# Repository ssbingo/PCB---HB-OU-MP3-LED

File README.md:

# PCB und Gehäuse für HB-OU-MP3-LED (jp112sdl)

## Bilder

## Schaltplan

[:arrow_right: Schaltplan](Images/HB-OU-MP3-LED_PCB_Schaltplan.pdf)

## Platine

[:arrow_right: PCB Gerber](Platine/HB-OU-MP3-LED_PCB.zip)

## Gehäuse

<br>

<br>

<br>

<br>

## Aufbau / Stückliste

### Der Aufbau

### Die benötigten Bauteile
| Bauteil | Link |
| --------|------|
| | |

## Hinweise

- :exclamation:

## Lizenz

**Creative Commons BY-NC-SA**<br>
Give Credit, NonCommercial, ShareAlike

<br />This work is licensed under a <a rel="license" href="http://creativecommons.org/licenses/by-nc-sa/4.0/">Creative Commons Attribution-NonCommercial-ShareAlike 4.0 International License</a>.

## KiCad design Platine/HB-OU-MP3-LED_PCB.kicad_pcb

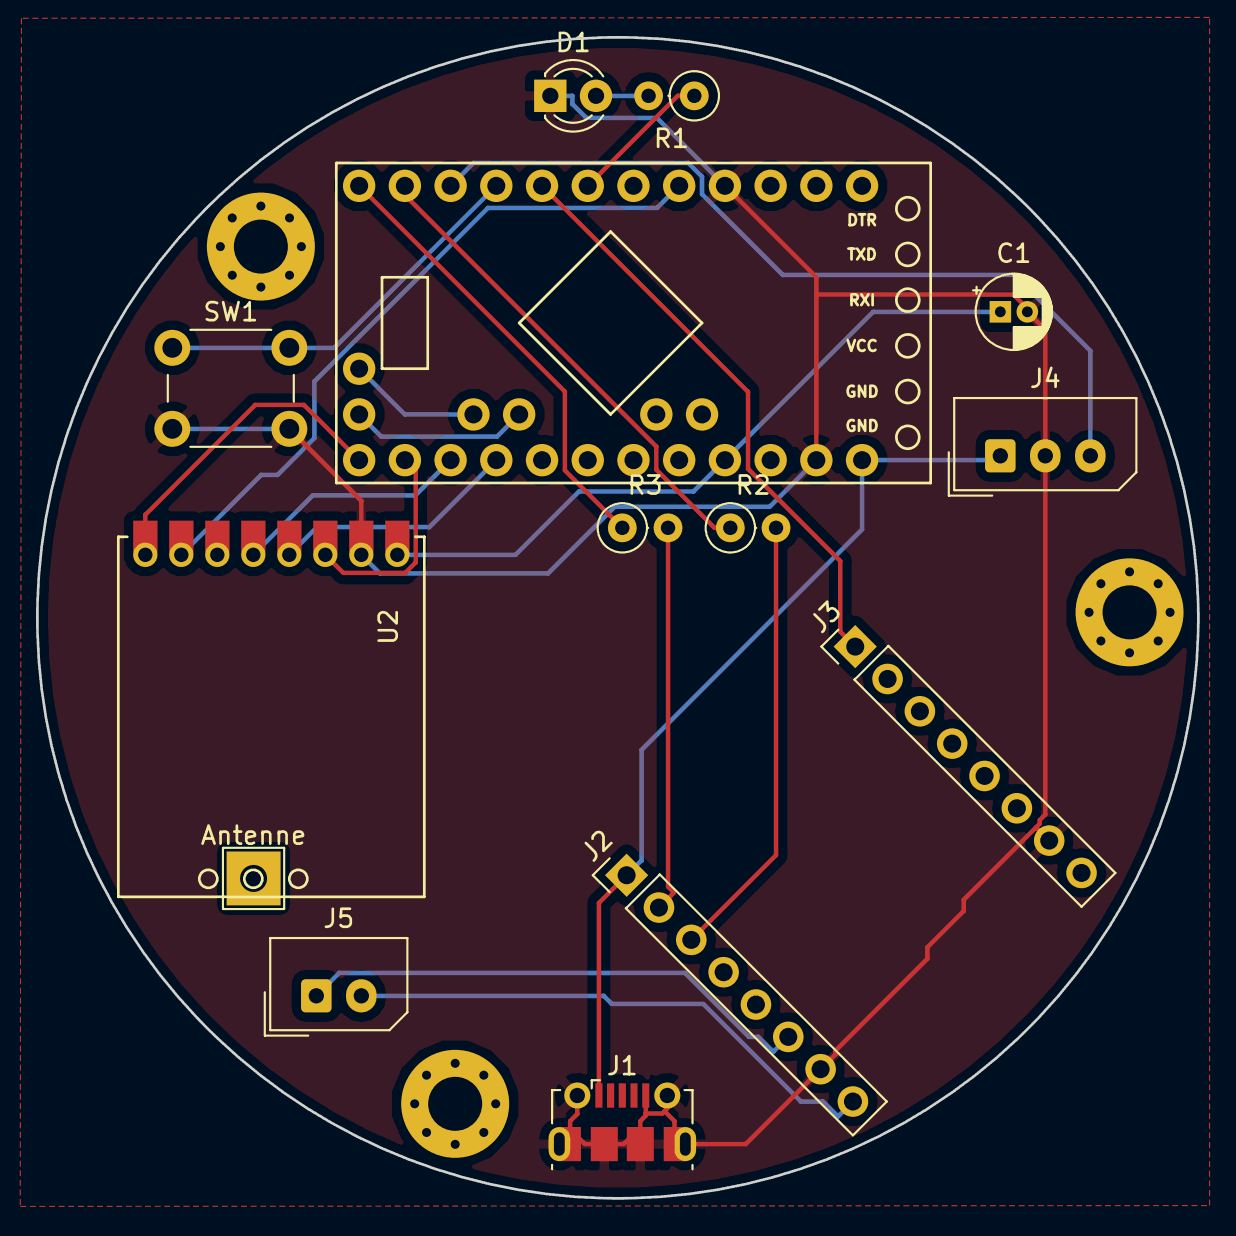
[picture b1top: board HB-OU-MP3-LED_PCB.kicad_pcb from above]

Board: 2 copper layers, 64.5 x 64.5 mm, 17 parts (0 on the bottom side), 19 nets.

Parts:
Antenne: TestPoint_THTPad_3.0x3.0mm_Drill1.5mm
C1: 10uF/15V; CP_Radial_D4.0mm_P1.50mm
D1: LED; LED_D3.0mm
J1: USB_B_Micro; USB_Micro-B_Molex-105017-0001
J2: DF-Mini Play 01; PinHeader_1x08_P2.54mm_Vertical
J3: DF-Mini Play 02; PinHeader_1x08_P2.54mm_Vertical
J4: LED WS2812B; Molex_SPOX_5267-03A_1x03_P2.50mm_Vertical
J5: Lautsprecher; Molex_SPOX_5267-02A_1x02_P2.50mm_Vertical
R1: 330; R_Axial_DIN0207_L6.3mm_D2.5mm_P2.54mm_Vertical
R2, R3: 1K; R_Axial_DIN0207_L6.3mm_D2.5mm_P2.54mm_Vertical
REF01, REF02, REF03: MountingHole_3mm_Pad_Via
SW1: CONFIG_BUTTON; SW_PUSH_6mm_H5mm
U1: ArduinoProMini
U2: CC1101

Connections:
+3V3: C1.1, U1.9, U2.1
+5V: J1.1, J2.1, J4.1, U1.12
/BUSY: J3.1, U1.20
/D2: U1.17, U2.7
/D_in: J4.3, U1.22
/MISO: U1.3, U2.5
/MOSI: U1.2, U2.3
/RX: J2.2, R3.2
/SCK: U1.4, U2.4
/SPK1: J2.6, J5.1
/SPK2: J2.8, J5.2
/SS: U1.1, U2.8
/TX: J2.3, R2.2
GND: C1.2, D1.1, J1.5, J1.6, J2.7, J3.7, J4.2, SW1.2, U1.11, U1.16, U2.2
unnamed: D1.2, R1.2
unnamed: R1.1, U1.19
unnamed: R2.1, U1.23
unnamed: R3.1, U1.24
unnamed: SW1.1, U1.21

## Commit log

2020-02-26 readm.md
